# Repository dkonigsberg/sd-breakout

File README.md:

# microSD Breakout Board

This repository contains the [KiCad](https://www.kicad.org/) project
with the complete circuit schematics and PCB layout for a microSD
card breakout board. This board includes all the necessary pull-up
resistors and protection diodes for the full SD interface, courtesy
of the EClamp2410P component.

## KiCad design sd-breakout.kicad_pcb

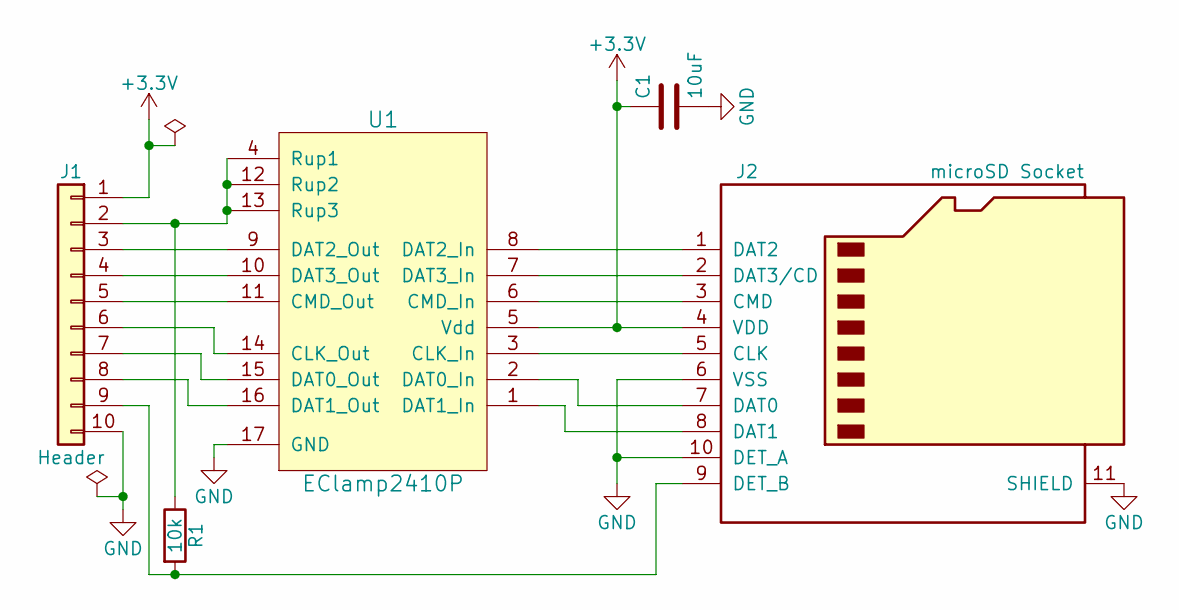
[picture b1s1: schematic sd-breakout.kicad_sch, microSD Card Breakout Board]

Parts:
C1: 10uF; C_0805_2012Metric; Manufacturer PN CL21A106KAFN3NE
J1: Header; PinHeader_1x10_P2.54mm_Vertical
J2: microSD Socket; microSD_HC_Hirose_DM3AT-SF-PEJM5; Manufacturer PN DM3AT-SF-PEJM5
R1: 10k; R_0805_2012Metric; Manufacturer PN CRCW080510K0JNEA
U1: EClamp2410P; SLP4016P16_1.6x4mm_P0.5mm; Manufacturer PN ECLAMP2410P.TCT

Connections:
+3V3: C1.1, J1.1, J2.4 (VDD), U1.5 (Vdd)
GND: C1.2, J1.10, J2.6 (VSS), J2.10 (DET_A), J2.11 (SHIELD), U1.17 (GND)
unnamed: J1.2, R1.1, U1.4 (Rup1), U1.12 (Rup2), U1.13 (Rup3)
unnamed: J1.3, U1.9 (DAT2_Out)
unnamed: J1.4, U1.10 (DAT3_Out)
unnamed: J1.5, U1.11 (CMD_Out)
unnamed: J1.6, U1.14 (CLK_Out)
unnamed: J1.7, U1.15 (DAT0_Out)
unnamed: J1.8, U1.16 (DAT1_Out)
unnamed: J1.9, J2.9 (DET_B), R1.2
unnamed: J2.1 (DAT2), U1.8 (DAT2_In)
unnamed: J2.2 (DAT3/CD), U1.7 (DAT3_In)
unnamed: J2.3 (CMD), U1.6 (CMD_In)
unnamed: J2.5 (CLK), U1.3 (CLK_In)
unnamed: J2.7 (DAT0), U1.2 (DAT0_In)
unnamed: J2.8 (DAT1), U1.1 (DAT1_In)

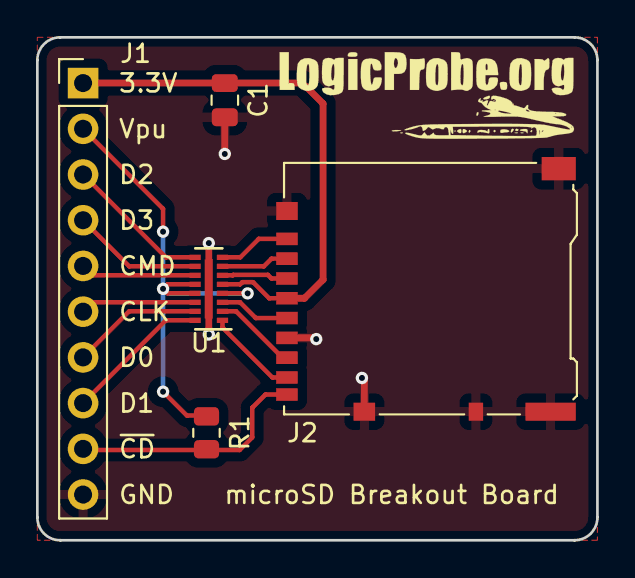
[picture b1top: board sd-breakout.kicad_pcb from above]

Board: 2 copper layers, 31.1 x 27.9 mm, 5 parts (0 on the bottom side), 16 nets.

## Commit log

2018-03-06 Initial commit for standalone SD breakout board project
2018-03-06 Finished layout and added logos
2018-06-10 Added BOM tool configuration file
2018-06-10 Added photo of assembled board
2018-06-10 Add image of schematic
2018-06-10 Updated footprint and model for EClamp chip
2018-06-10 Component 3D model updates
2018-06-10 Add image of 3D PCB model
2018-06-10 Added README and LICENSE files
2018-06-10 Update README.md
    Fixed image blob paths
2018-06-10 Update README.md
    Another path fix
2022-01-01 Updated project to KiCad v6
2022-01-01 Fix KiCad project URL
